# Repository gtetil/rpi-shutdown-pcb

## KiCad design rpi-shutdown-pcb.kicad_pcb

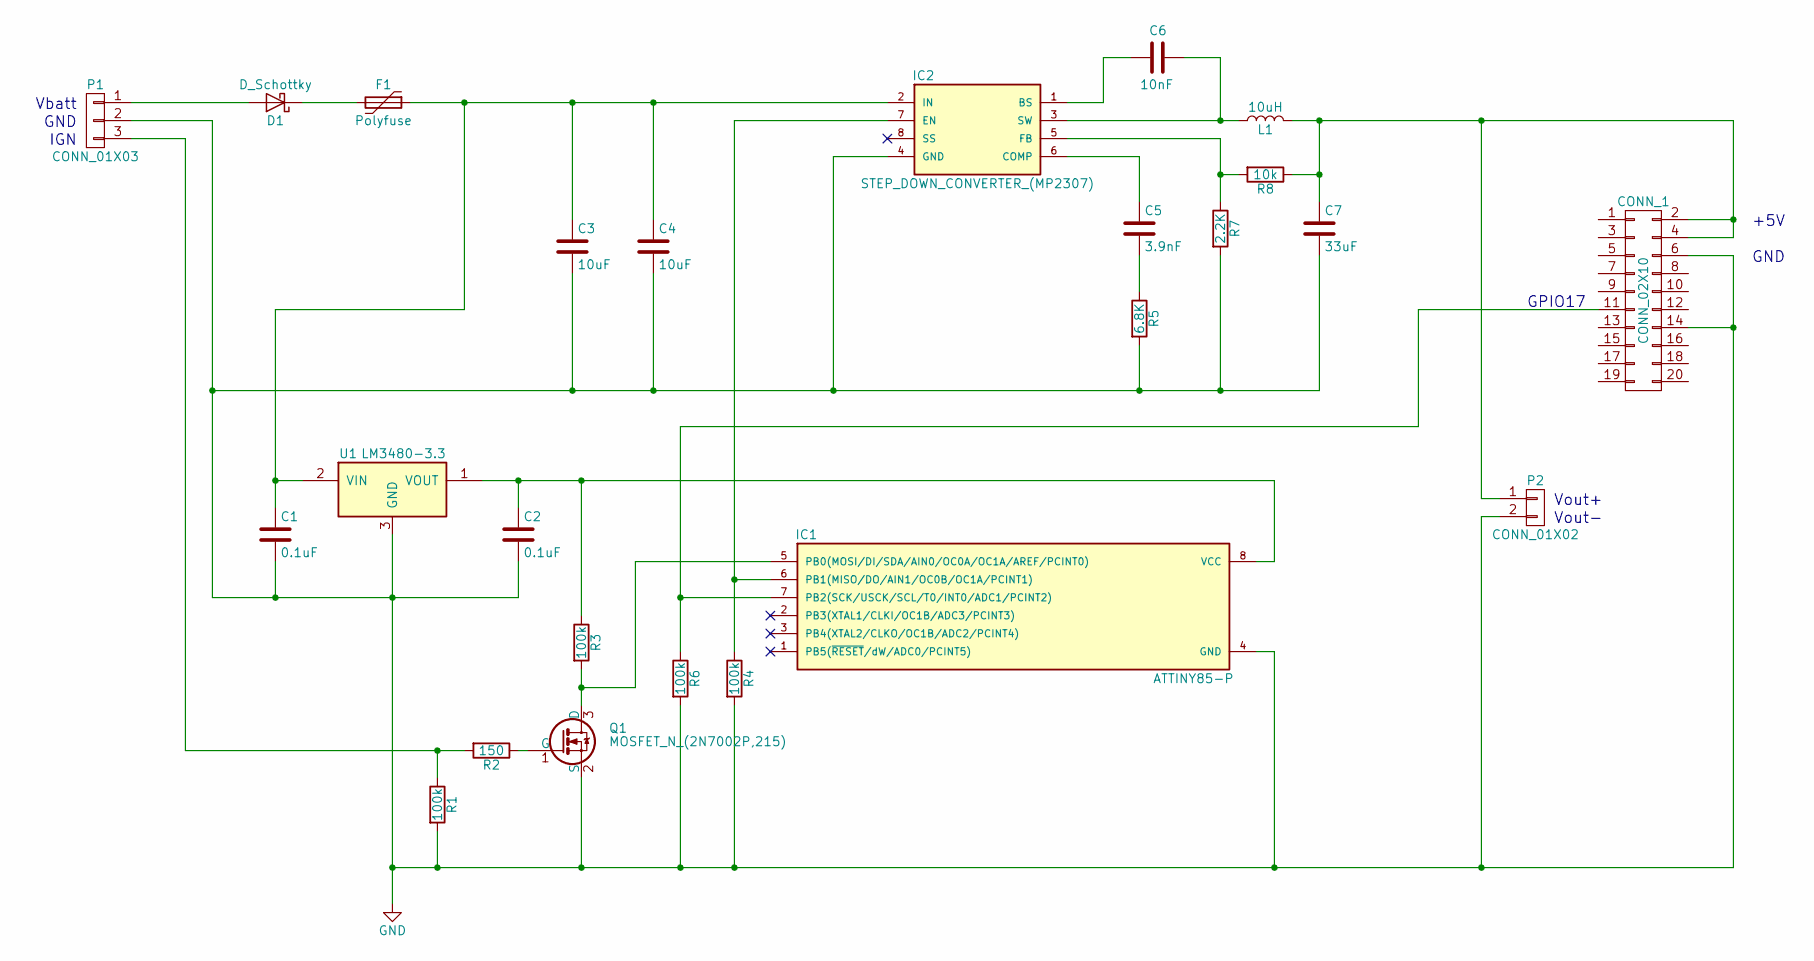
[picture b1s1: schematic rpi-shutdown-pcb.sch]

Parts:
C1, C2: 0.1uF; R_1206_HandSoldering_(narrow)
C3, C4: 10uF; R_1206_HandSoldering_(narrow)
C5: 3.9nF; C_0805_HandSoldering_(narrow)
C6: 10nF; C_0805_HandSoldering_(narrow)
C7: 33uF; R_1206_HandSoldering_(narrow)
CONN_1: CONN_02X10; HEADER_20_PIN_FEMALE_(PPTC102LFBN-RC)
D1: D_Schottky; DO-214AB
F1: Polyfuse; R_1812_HandSoldering
IC1: ATTINY85-P; DIP-8_W7.62mm
IC2: STEP_DOWN_CONVERTER_(MP2307); SOIC8N_(EXPOSED_PAD)
L1: 10uH; INDUCTOR_10uH_(ASPI-0630LR)
P1: CONN_01X03; 3_PADS_FOR_18_AWG_WIRE
P2: CONN_01X02; 2_PADS_FOR_18_AWG_WIRE
Q1: MOSFET_N_(2N7002P,215); SOT-23_Handsoldering
R1, R3, R4, R6: 100k; R_1206_HandSoldering_(narrow)
R2: 150; R_1206_HandSoldering_(narrow)
R5: 6.8K; R_1206_HandSoldering_(narrow)
R7: 2.2K; R_1206_HandSoldering_(narrow)
R8: 10k; R_1206_HandSoldering_(narrow)
U1: LM3480-3.3; SOT-23_Handsoldering

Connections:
GND: C1.2, C2.2, C3.2, C4.2, C7.2, CONN_1.6, CONN_1.14, IC1.4 (GND), IC2.4 (GND), IC2.9 (GND), P1.2, P2.2, Q1.2 (S), R1.2, R4.2, R5.2, R6.2, R7.2, U1.3 (GND)
unnamed: C1.1, C3.1, C4.1, F1.1, IC2.2 (IN), U1.2 (VIN)
unnamed: C2.1, IC1.8 (VCC), R3.1, U1.1 (VOUT)
unnamed: C5.1, IC2.6 (COMP)
unnamed: C5.2, R5.1
unnamed: C6.1, IC2.3 (SW), L1.1
unnamed: C6.2, IC2.1 (BS)
unnamed: C7.1, CONN_1.2, CONN_1.4, L1.2, P2.1, R8.1
unnamed: CONN_1.11, IC1.7 (PB2(SCK/USCK/SCL/T0/INT0/ADC1/PCINT2)), R6.1
unnamed: D1.1 (K), F1.2
unnamed: D1.2 (A), P1.1
unnamed: IC1.5 (PB0(MOSI/DI/SDA/AIN0/OC0A/OC1A/AREF/PCI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), Q1.3 (D), R3.2
unnamed: IC1.6 (PB1(MISO/DO/AIN1/OC0B/OC1A/PCINT1)), IC2.7 (EN), R4.1
unnamed: IC2.5 (FB), R7.1, R8.2
unnamed: P1.3, R1.1, R2.2
unnamed: Q1.1 (G), R2.1

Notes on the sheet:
Vbatt
GND
IGN
Vout+
Vout-
GPIO17
+5V

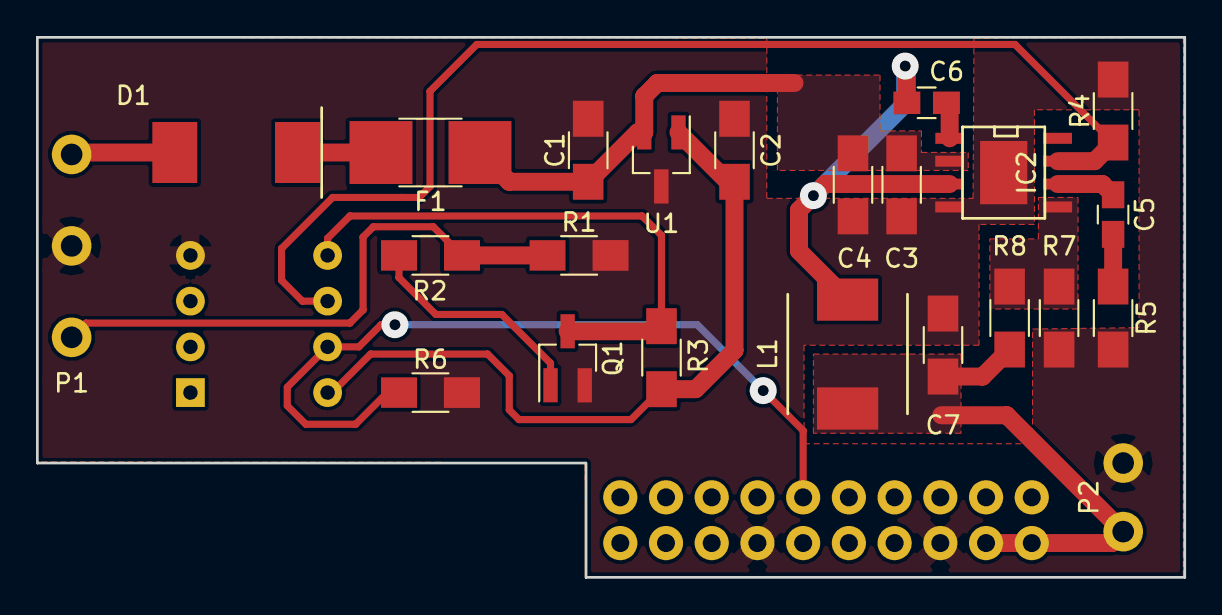
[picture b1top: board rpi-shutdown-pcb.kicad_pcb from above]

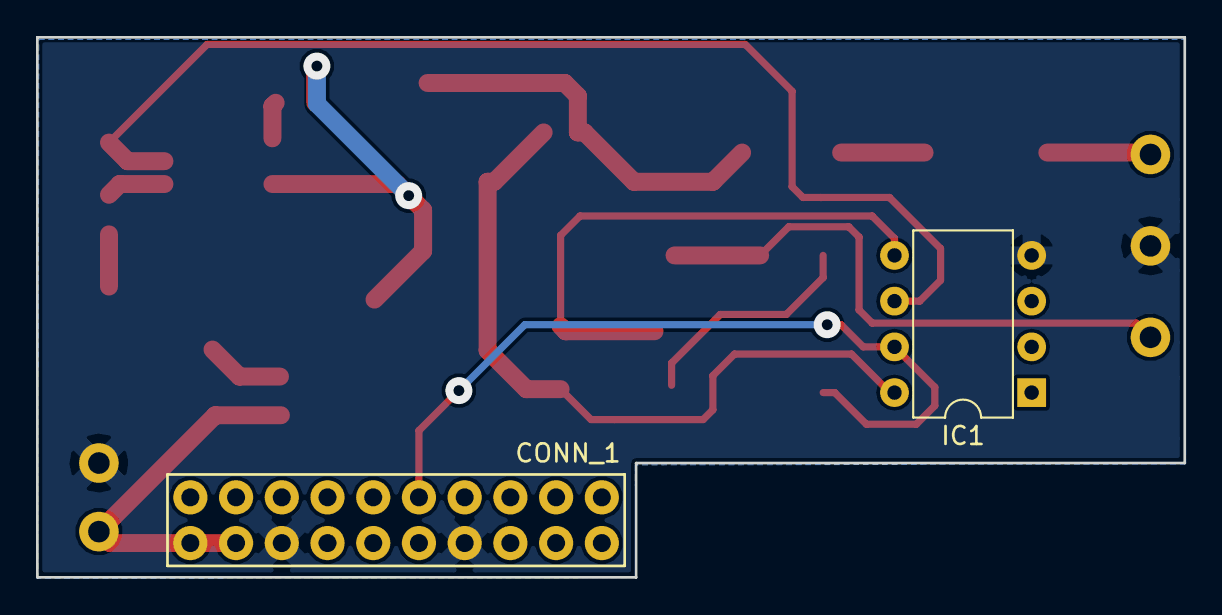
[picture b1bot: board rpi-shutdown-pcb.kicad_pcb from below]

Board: 2 copper layers, 63.7 x 30.0 mm, 25 parts (2 on the bottom side), 16 nets.

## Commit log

2017-03-28 finished revised circuit with P-channel FET and footprints
2017-03-30 -finished pcb layout.
2017-03-31 created gerbers and lmd file.
2017-06-14 Finished adding step-down converter circuit. Need to start on footprints.
2017-06-18 Finished footprints.
2017-06-25 Finished PCB layout. Ready to try routing.
2017-09-10 - Rearranged board to hopefully get better voltage regulation.
